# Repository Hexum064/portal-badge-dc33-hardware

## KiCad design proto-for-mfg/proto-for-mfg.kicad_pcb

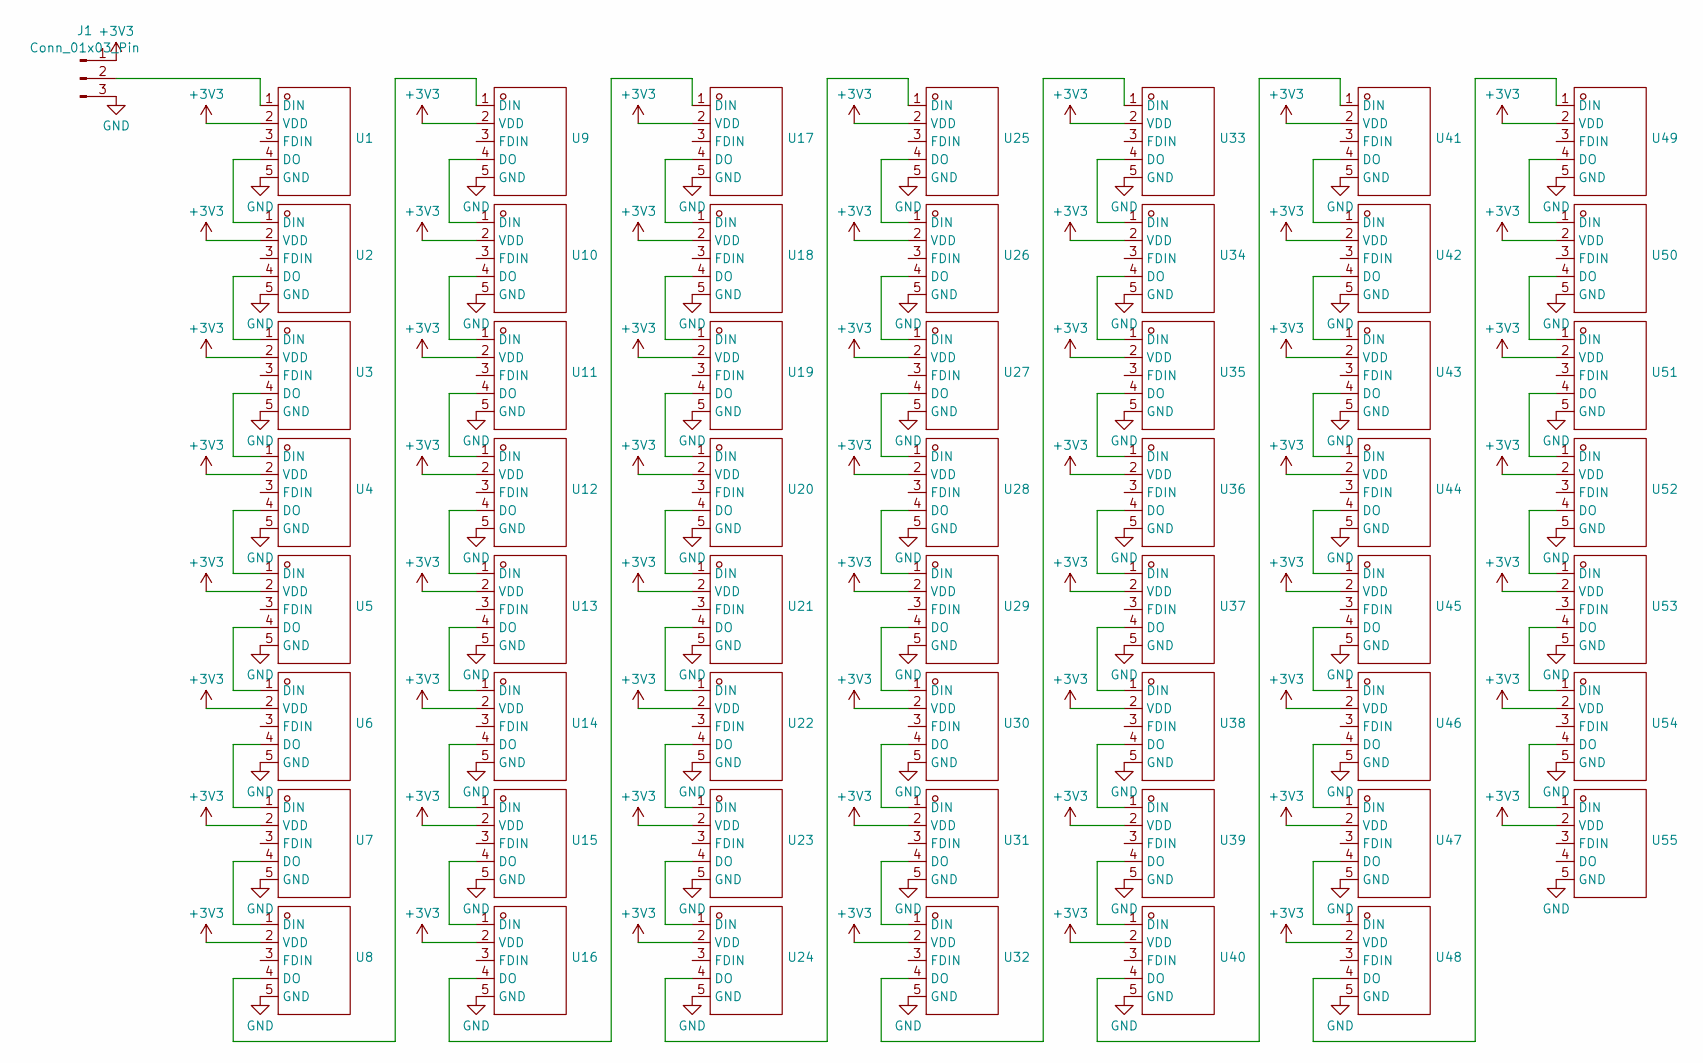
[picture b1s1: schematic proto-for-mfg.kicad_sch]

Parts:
J1: Conn_01x03_Pin; PinHeader_1x03_P2.54mm_Vertical
U1, U2, U3, U4, U5, U6, U7, U8, U9, U10, U11, U12, U13, U14, U15, U16, U17, U18, U19, U20, U21, U22, U23, U24, U25, U26, U27, U28, U29, U30, U31, U32, U33, U34, U35, U36, U37, U38, U39, U40, U41, U42, U43, U44, U45, U46, U47, U48, U49, U50, U51, U52, U53, U54, U55: LED-SMD_5P-L3.2-W1.4_TX1813Y5; Manufacturer Part TX1813Y5; LCSC Part Name TX1813Y5

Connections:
+3V3: J1.1, U1.2 (VDD), U2.2 (VDD), U3.2 (VDD), U4.2 (VDD), U5.2 (VDD), U6.2 (VDD), U7.2 (VDD), U8.2 (VDD), U9.2 (VDD), U10.2 (VDD), U11.2 (VDD), U12.2 (VDD), U13.2 (VDD), U14.2 (VDD), U15.2 (VDD), U16.2 (VDD), U17.2 (VDD), U18.2 (VDD), U19.2 (VDD), U20.2 (VDD), U21.2 (VDD), U22.2 (VDD), U23.2 (VDD), U24.2 (VDD), U25.2 (VDD), U26.2 (VDD), U27.2 (VDD), U28.2 (VDD), U29.2 (VDD), U30.2 (VDD), U31.2 (VDD), U32.2 (VDD), U33.2 (VDD), U34.2 (VDD), U35.2 (VDD), U36.2 (VDD), U37.2 (VDD), U38.2 (VDD), U39.2 (VDD), U40.2 (VDD), U41.2 (VDD), U42.2 (VDD), U43.2 (VDD), U44.2 (VDD), U45.2 (VDD), U46.2 (VDD), U47.2 (VDD), U48.2 (VDD), U49.2 (VDD), U50.2 (VDD), U51.2 (VDD), U52.2 (VDD), U53.2 (VDD), U54.2 (VDD), U55.2 (VDD)
GND: J1.3, U1.5 (GND), U2.5 (GND), U3.5 (GND), U4.5 (GND), U5.5 (GND), U6.5 (GND), U7.5 (GND), U8.5 (GND), U9.5 (GND), U10.5 (GND), U11.5 (GND), U12.5 (GND), U13.5 (GND), U14.5 (GND), U15.5 (GND), U16.5 (GND), U17.5 (GND), U18.5 (GND), U19.5 (GND), U20.5 (GND), U21.5 (GND), U22.5 (GND), U23.5 (GND), U24.5 (GND), U25.5 (GND), U26.5 (GND), U27.5 (GND), U28.5 (GND), U29.5 (GND), U30.5 (GND), U31.5 (GND), U32.5 (GND), U33.5 (GND), U34.5 (GND), U35.5 (GND), U36.5 (GND), U37.5 (GND), U38.5 (GND), U39.5 (GND), U40.5 (GND), U41.5 (GND), U42.5 (GND), U43.5 (GND), U44.5 (GND), U45.5 (GND), U46.5 (GND), U47.5 (GND), U48.5 (GND), U49.5 (GND), U50.5 (GND), U51.5 (GND), U52.5 (GND), U53.5 (GND), U54.5 (GND), U55.5 (GND)
unnamed: J1.2, U1.1 (DIN)
unnamed: U1.4 (DO), U2.1 (DIN)
unnamed: U2.4 (DO), U3.1 (DIN)
unnamed: U3.4 (DO), U4.1 (DIN)
unnamed: U4.4 (DO), U5.1 (DIN)
unnamed: U5.4 (DO), U6.1 (DIN)
unnamed: U6.4 (DO), U7.1 (DIN)
unnamed: U7.4 (DO), U8.1 (DIN)
unnamed: U8.4 (DO), U9.1 (DIN)
unnamed: U9.4 (DO), U10.1 (DIN)
unnamed: U10.4 (DO), U11.1 (DIN)
unnamed: U11.4 (DO), U12.1 (DIN)
unnamed: U12.4 (DO), U13.1 (DIN)
unnamed: U13.4 (DO), U14.1 (DIN)
unnamed: U14.4 (DO), U15.1 (DIN)
unnamed: U15.4 (DO), U16.1 (DIN)
unnamed: U16.4 (DO), U17.1 (DIN)
unnamed: U17.4 (DO), U18.1 (DIN)
unnamed: U18.4 (DO), U19.1 (DIN)
unnamed: U19.4 (DO), U20.1 (DIN)
unnamed: U20.4 (DO), U21.1 (DIN)
unnamed: U21.4 (DO), U22.1 (DIN)
unnamed: U22.4 (DO), U23.1 (DIN)
unnamed: U23.4 (DO), U24.1 (DIN)
unnamed: U24.4 (DO), U25.1 (DIN)
unnamed: U25.4 (DO), U26.1 (DIN)
unnamed: U26.4 (DO), U27.1 (DIN)
unnamed: U27.4 (DO), U28.1 (DIN)
unnamed: U28.4 (DO), U29.1 (DIN)
unnamed: U29.4 (DO), U30.1 (DIN)
unnamed: U30.4 (DO), U31.1 (DIN)
unnamed: U31.4 (DO), U32.1 (DIN)
unnamed: U32.4 (DO), U33.1 (DIN)
unnamed: U33.4 (DO), U34.1 (DIN)
unnamed: U34.4 (DO), U35.1 (DIN)
unnamed: U35.4 (DO), U36.1 (DIN)
unnamed: U36.4 (DO), U37.1 (DIN)
unnamed: U37.4 (DO), U38.1 (DIN)
unnamed: U38.4 (DO), U39.1 (DIN)
unnamed: U39.4 (DO), U40.1 (DIN)
unnamed: U40.4 (DO), U41.1 (DIN)
unnamed: U41.4 (DO), U42.1 (DIN)
unnamed: U42.4 (DO), U43.1 (DIN)
unnamed: U43.4 (DO), U44.1 (DIN)
unnamed: U44.4 (DO), U45.1 (DIN)
unnamed: U45.4 (DO), U46.1 (DIN)
unnamed: U46.4 (DO), U47.1 (DIN)
unnamed: U47.4 (DO), U48.1 (DIN)
unnamed: U48.4 (DO), U49.1 (DIN)
unnamed: U49.4 (DO), U50.1 (DIN)
unnamed: U50.4 (DO), U51.1 (DIN)
unnamed: U51.4 (DO), U52.1 (DIN)
unnamed: U52.4 (DO), U53.1 (DIN)
unnamed: U53.4 (DO), U54.1 (DIN)
unnamed: U54.4 (DO), U55.1 (DIN)

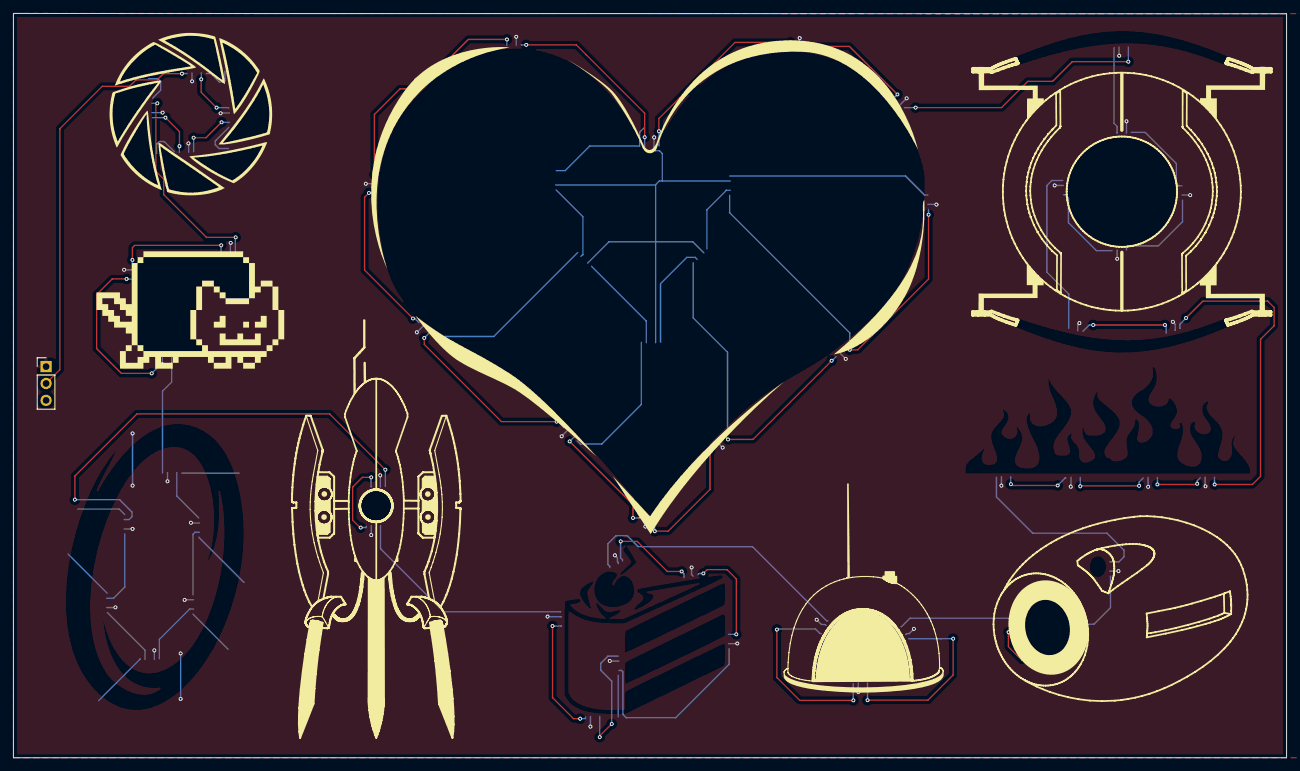
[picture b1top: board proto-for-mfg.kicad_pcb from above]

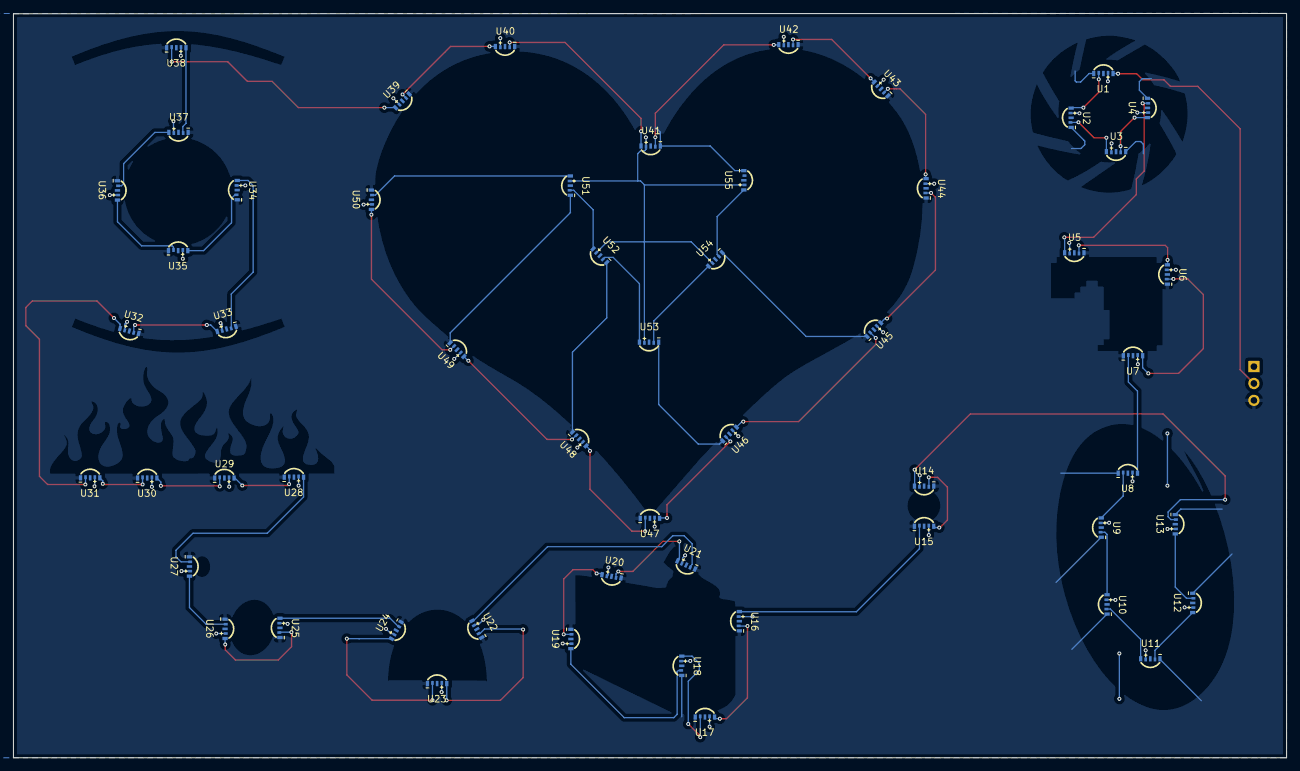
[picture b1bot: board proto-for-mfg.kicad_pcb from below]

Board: 2 copper layers, 191.4 x 111.9 mm, 56 parts (55 on the bottom side), 57 nets.

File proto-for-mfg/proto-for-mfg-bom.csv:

Designation,Comment,JLCPCB Part #,Footprint,Qty
"U1,U2,U3,U4,U5,U6,U7,U8,U9,U10,U11,U12,U13,U14,U15,U16,U17,U18,U19,U20,U21,U22,U23,U24,U25,U26,U27,U28,U29,U30,U31,U32,U33,U34,U35,U36,U37,U38,U39,U40,U41,U42,U43,U44,U45,U46,U47,U48,U49,U50,U51,U52,U53,U54,U55,U56",SK6812D-EC3210R,C2890041,"SMD,1.1x3.2mm",65

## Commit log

2025-04-02 move over to new LED and fix design
2025-04-17 adding a version with cutouts
2025-04-26 added more cutouts
